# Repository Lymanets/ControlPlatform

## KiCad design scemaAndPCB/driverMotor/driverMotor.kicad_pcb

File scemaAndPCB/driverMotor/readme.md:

**Плата и схема драйвера двигателей 

**Kicad

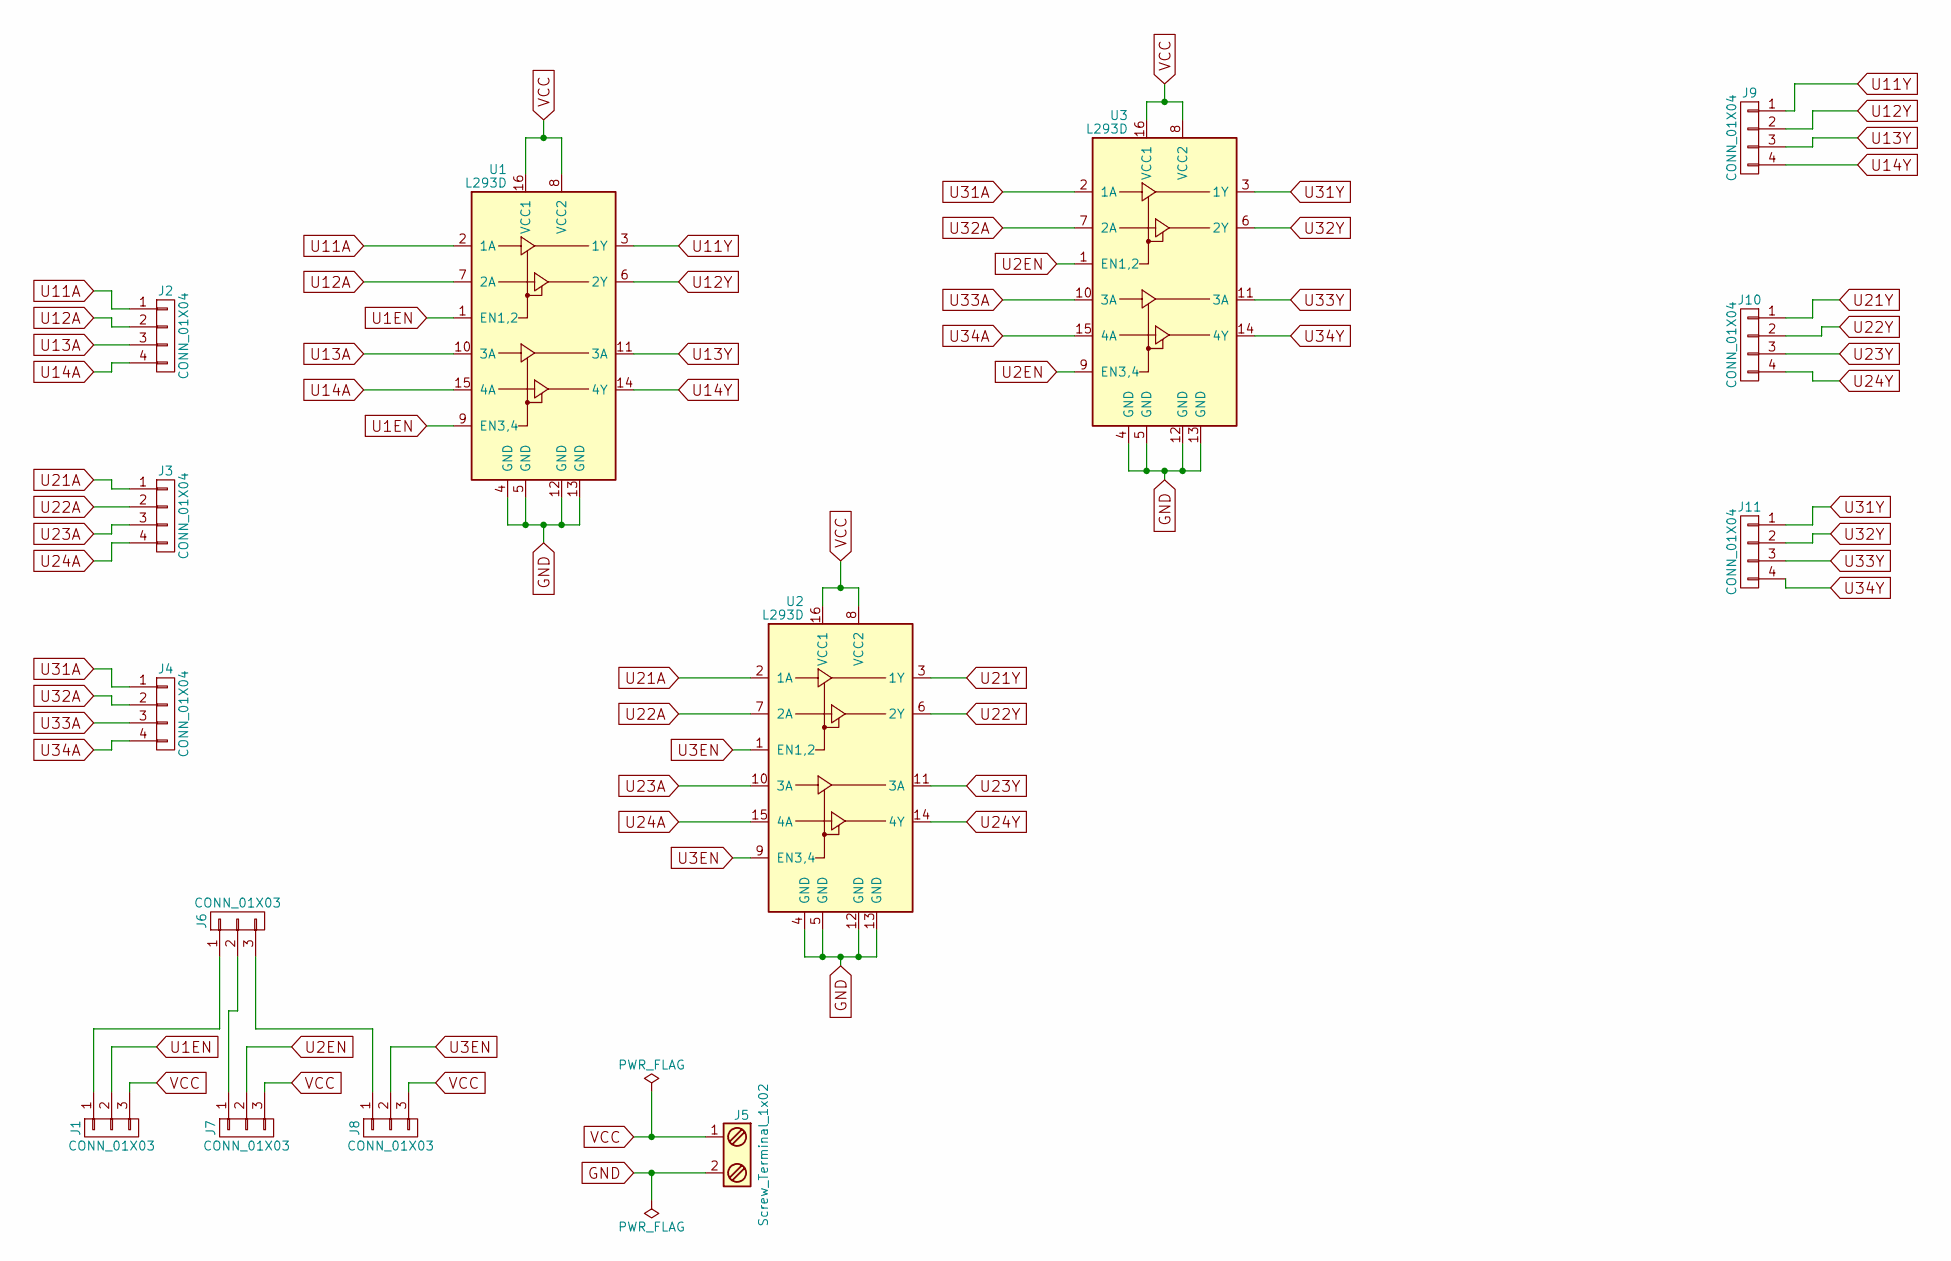
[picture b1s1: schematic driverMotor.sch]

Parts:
J1, J6, J7, J8: CONN_01X03; Pin_Header_Angled_1x03_Pitch2.54mm
J2, J3, J4, J9, J10, J11: CONN_01X04; Pin_Header_Angled_1x04_Pitch2.54mm
J5: Screw_Terminal_1x02; TerminalBlock_Pheonix_MKDS1.5-2pol
U1, U2, U3: L293D; DIP-16_W7.62mm_LongPads

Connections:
GND: J5.2, U1.4 (GND), U1.5 (GND), U1.12 (GND), U1.13 (GND), U2.4 (GND), U2.5 (GND), U2.12 (GND), U2.13 (GND), U3.4 (GND), U3.5 (GND), U3.12 (GND), U3.13 (GND)
unnamed: J1.1, J6.1
unnamed: J6.2, J7.1
unnamed: J6.3, J8.1
U1EN: J1.2, U1.1 (EN1,2), U1.9 (EN3,4)
U2EN: J7.2, U3.1 (EN1,2), U3.9 (EN3,4)
U3EN: J8.2, U2.1 (EN1,2), U2.9 (EN3,4)
U11A: J2.1, U1.2 (1A)
U11Y: J9.1, U1.3 (1Y)
U12A: J2.2, U1.7 (2A)
U12Y: J9.2, U1.6 (2Y)
U13A: J2.3, U1.10 (3A)
U13Y: J9.3, U1.11 (3A)
U14A: J2.4, U1.15 (4A)
U14Y: J9.4, U1.14 (4Y)
U21A: J3.1, U2.2 (1A)
U21Y: J10.1, U2.3 (1Y)
U22A: J3.2, U2.7 (2A)
U22Y: J10.2, U2.6 (2Y)
U23A: J3.3, U2.10 (3A)
U23Y: J10.3, U2.11 (3A)
U24A: J3.4, U2.15 (4A)
U24Y: J10.4, U2.14 (4Y)
U31A: J4.1, U3.2 (1A)
U31Y: J11.1, U3.3 (1Y)
U32A: J4.2, U3.7 (2A)
U32Y: J11.2, U3.6 (2Y)
U33A: J4.3, U3.10 (3A)
U33Y: J11.3, U3.11 (3A)
U34A: J4.4, U3.15 (4A)
U34Y: J11.4, U3.14 (4Y)
VCC: J1.3, J5.1, J7.3, J8.3, U1.8 (VCC2), U1.16 (VCC1), U2.8 (VCC2), U2.16 (VCC1), U3.8 (VCC2), U3.16 (VCC1)

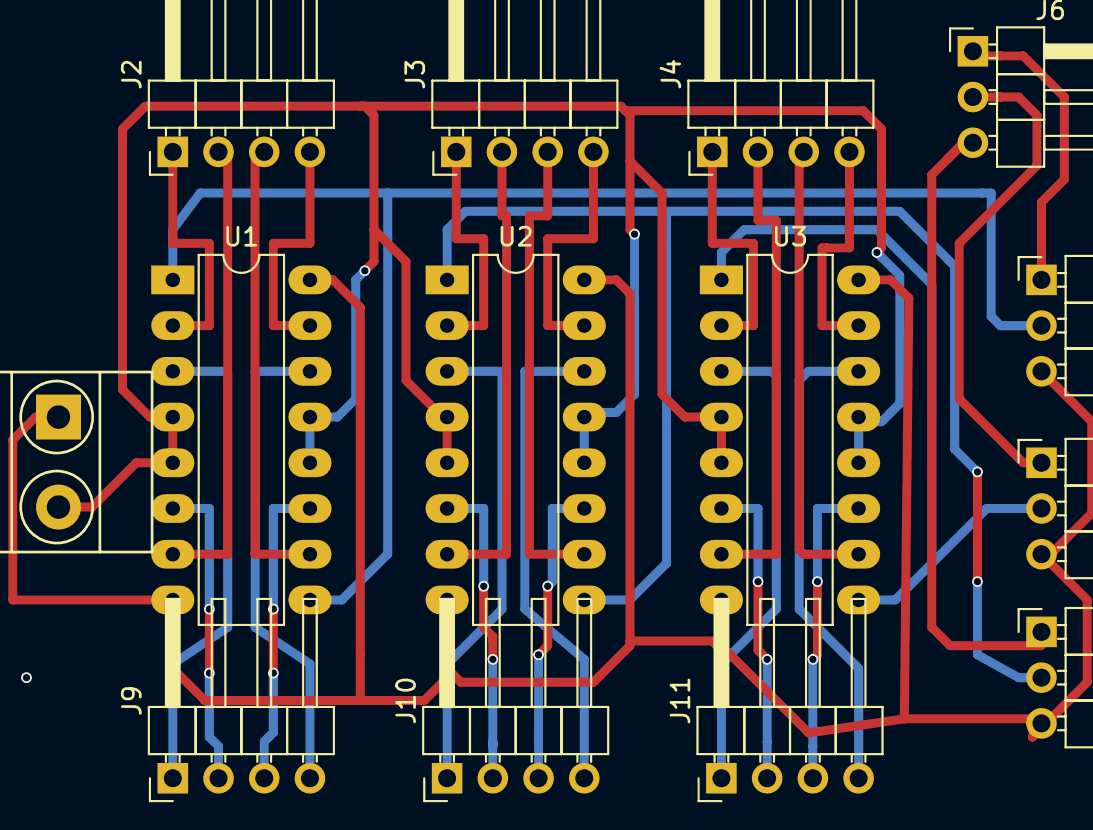
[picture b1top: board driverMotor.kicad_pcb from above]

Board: 2 copper layers, 14 parts (0 on the bottom side), 32 nets.

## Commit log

2017-05-02 Add text.txt
2017-05-11 Plata
